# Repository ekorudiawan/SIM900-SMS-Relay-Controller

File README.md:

# SIM900-SMS-Relay-Controller
SIM900 SMS Relay Controller

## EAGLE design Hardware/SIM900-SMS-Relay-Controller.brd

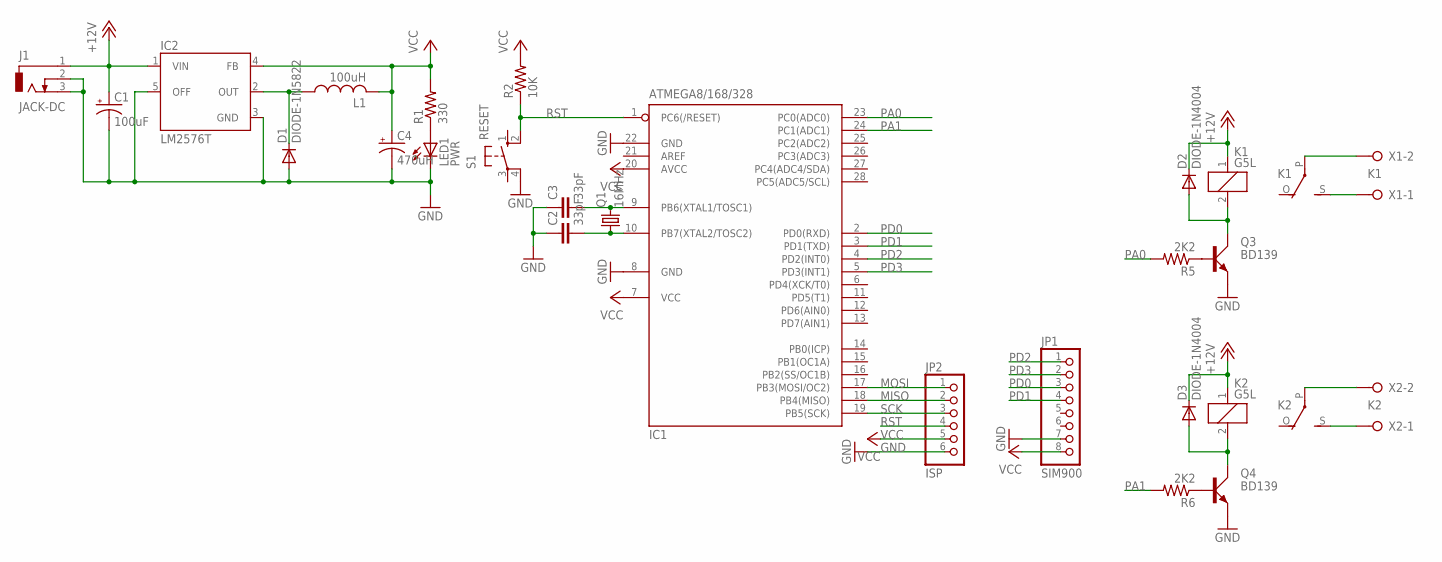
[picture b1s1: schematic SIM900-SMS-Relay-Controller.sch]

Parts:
C1: 100uF; E2,5-6
C2, C3: 33pF; C025-024X044
C4: 470uH; E3,5-8
D1: DIODE-1N5822; DO201-15
D2, D3: DIODE-1N4004; DO41-10
IC1: ATMEGA8/168/328; DIL28-3
IC2: LM2576T; TO220-5
J1: JACK-DC; DCJ0202
JP1: SIM900; 1X08
JP2: ISP; 1X06
K1, K2: G5L; G5LE
L1: 100uH; TJ3-U2
LED1: PWR; LED3MM
Q1: 16MHz; HC49/S
Q3, Q4: BD139; TO126AV
R1: 330; 0207/10
R2: 10K; 0207/10
R5, R6: 2K2; 0207/10
S1: RESET; B3F-10XX
X1: K1; W237-132
X2: K2; W237-132

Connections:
+12V: C1.+, D2.C, D3.C, IC2.1 (VIN), J1.1, K1.1, K2.1
GND: C1.-, C2.1, C3.1, C4.-, D1.A, IC1.8 (GND), IC1.22 (GND), IC2.3 (GND), IC2.5 (OFF), J1.2, J1.3, JP1.7, JP2.6, LED1.K (C), Q3.E, Q4.E, S1.4 (P1)
MISO: IC1.18 (PB4(MISO)), JP2.2
MOSI: IC1.17 (PB3(MOSI/OC2)), JP2.1
unnamed: C3.2, IC1.9 (PB6(XTAL1/TOSC1)), Q1.2
unnamed: C2.2, IC1.10 (PB7(XTAL2/TOSC2)), Q1.1
unnamed: K1.S, X1.1
unnamed: D1.C, IC2.2 (OUT), L1.1
unnamed: Q3.B, R5.1
unnamed: LED1.A, R1.1
unnamed: Q4.B, R6.1
unnamed: D2.A, K1.2, Q3.C
unnamed: D3.A, K2.2, Q4.C
unnamed: K1.P, X1.2
unnamed: K2.S, X2.1
unnamed: K2.P, X2.2
PA0: IC1.23 (PC0(ADC0)), R5.2
PA1: IC1.24 (PC1(ADC1)), R6.2
PD0: IC1.2 (PD0(RXD)), JP1.3
PD1: IC1.3 (PD1(TXD)), JP1.4
PD2: IC1.4 (PD2(INT0)), JP1.1
PD3: IC1.5 (PD3(INT1)), JP1.2
RST: IC1.1 (PC6(/RESET)), JP2.4, R2.1, S1.2 (S1)
SCK: IC1.19 (PB5(SCK)), JP2.3
VCC: C4.+, IC1.7 (VCC), IC1.20 (AVCC), IC2.4 (FB), JP1.8, JP2.5, L1.2, R1.2, R2.2

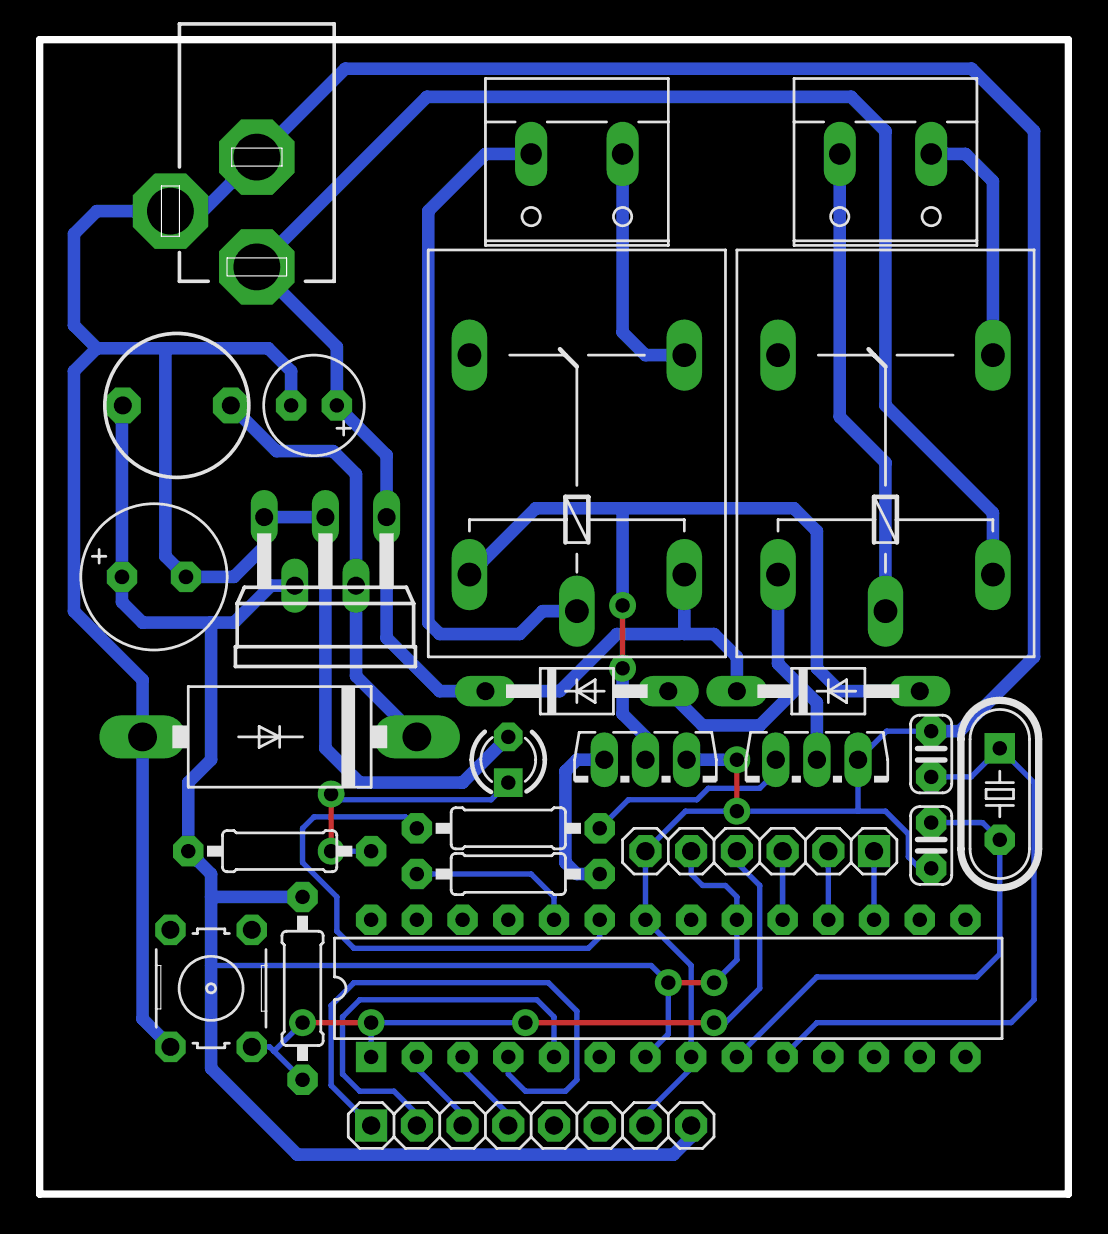
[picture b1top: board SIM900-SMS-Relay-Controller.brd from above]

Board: 2 copper layers, 57.2 x 64.1 mm, 26 parts (0 on the bottom side), 25 nets.

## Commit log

2017-10-03 Added HW & SW Files
